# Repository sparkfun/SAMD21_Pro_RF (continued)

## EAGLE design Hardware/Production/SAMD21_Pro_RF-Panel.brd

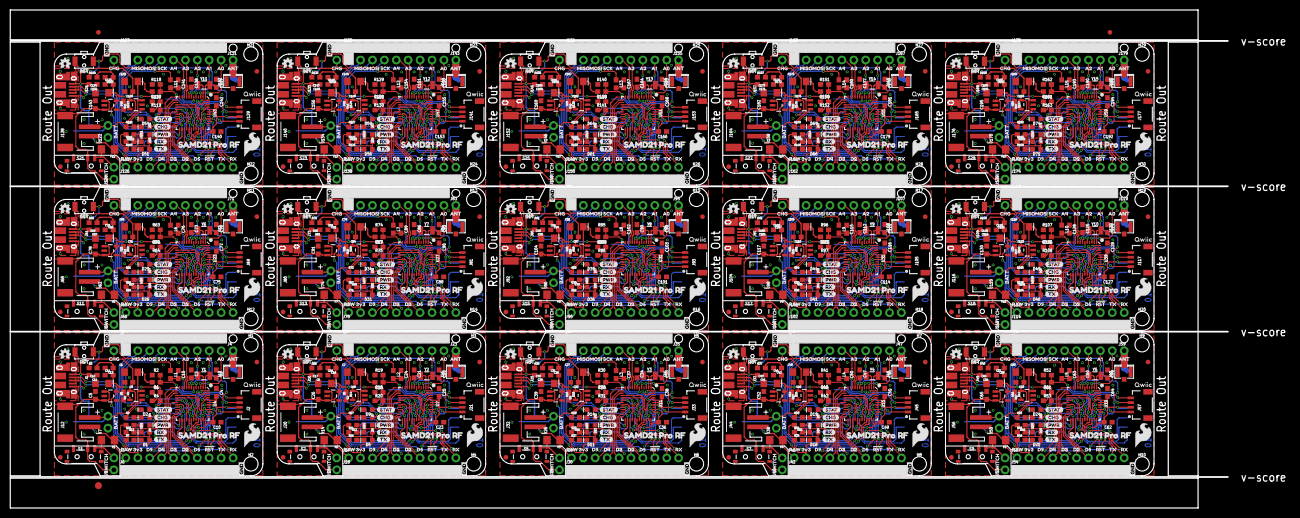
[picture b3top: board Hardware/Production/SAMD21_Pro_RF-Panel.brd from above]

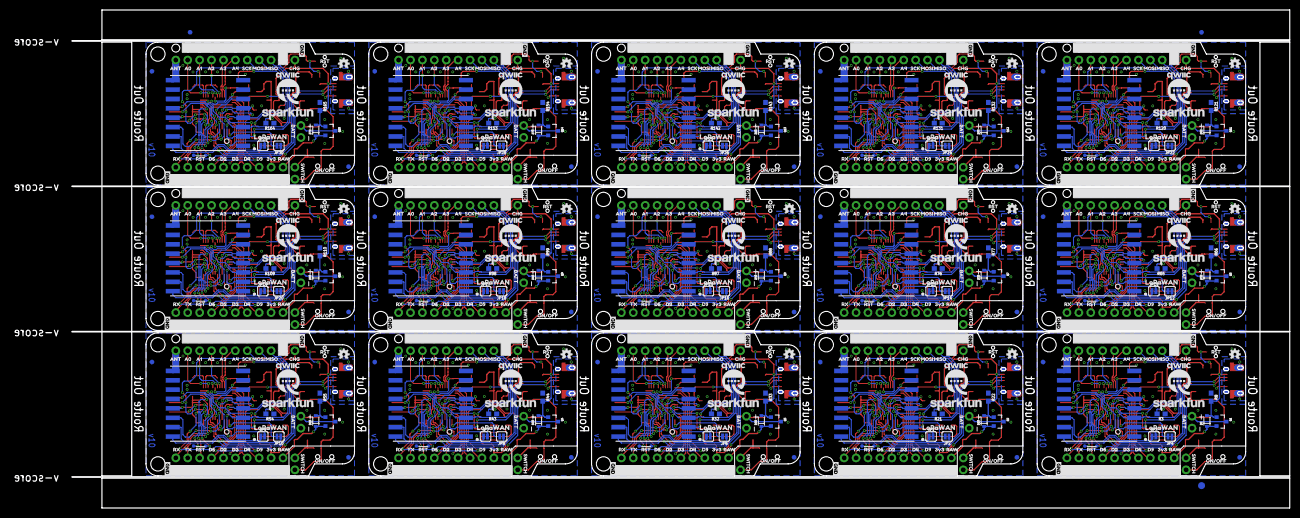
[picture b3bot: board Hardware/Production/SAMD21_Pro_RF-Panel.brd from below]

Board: 2 copper layers, 259.6 x 106.2 mm, 1911 parts (633 on the bottom side), 780 nets.

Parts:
C1, C7, C13, C17, C27, C30, C40, C43, C53, C56, C66, C69, C79, C82, C92, C95, C105, C108, C118, C121, C131, C134, C144, C147, C157, C160, C170, C173, C183, C186: 10uF; EIA3216
C2, C3, C20, C21, C33, C34, C46, C47, C59, C60, C72, C73, C85, C86, C98, C99, C111, C112, C124, C125, C137, C138, C150, C151, C163, C164, C176, C177, C189, C190: 15pF; 0603
C4, C6, C8, C10, C11, C14, C15, C18, C22, C23, C24, C25, C28, C31, C35, C36, C37, C38, C41, C44, C48, C49, C50, C51, C54, C57, C61, C62, C63, C64, C67, C70, C74, C75, C76, C77, C80, C83, C87, C88, C89, C90, C93, C96, C100, C101, C102, C103, C106, C109, C113, C114, C115, C116, C119, C122, C126, C127, C128, C129, C132, C135, C139, C140, C141, C142, C145, C148, C152, C153, C154, C155, C158, C161, C165, C166, C167, C168, C171, C174, C178, C179, C180, C181, C184, C187, C191, C192, C193, C194: 0.1uF; 0603
C5, C12, C16, C26, C29, C39, C42, C52, C55, C65, C68, C78, C81, C91, C94, C104, C107, C117, C120, C130, C133, C143, C146, C156, C159, C169, C172, C182, C185, C195: 1.0uF; 0603
C9, C19, C32, C45, C58, C71, C84, C97, C110, C123, C136, C149, C162, C175, C188: 4.7uF; 0603
D1, D5, D11, D16, D21, D26, D31, D36, D41, D46, D51, D56, D61, D66, D71: Green; LED-0603
D2, D4, D7, D9, D12, D14, D17, D19, D22, D24, D27, D29, D32, D34, D37, D39, D42, D44, D47, D49, D52, D54, D57, D59, D62, D64, D67, D69, D72, D74: BLUE; LED-0603
D3, D10, D15, D20, D25, D30, D35, D40, D45, D50, D55, D60, D65, D70, D75: BAT20J; SOD-323
D6, D8, D13, D18, D23, D28, D33, D38, D43, D48, D53, D58, D63, D68, D73: Yellow; LED-0603
E$1, E$2, E$3, E$4: FIDUCIAL-1X2
E$5, E$6: FIDUCIAL-1.5X3
F1, F2, F3, F4, F5, F6, F7, F8, F9, F10, F11, F12, F13, F14, F15: 6V/0.5A; 1206
FD1, FD2, FD3, FD4, FD5, FD6, FD7, FD8, FD9, FD10, FD11, FD12, FD13, FD14, FD15, FD16, FD17, FD18, FD19, FD20, FD21, FD22, FD23, FD24, FD25, FD26, FD27, FD28, FD29, FD30, FD31, FD32, FD33, FD34, FD35, FD36, FD37, FD38, FD39, FD40, FD41, FD42, FD43, FD44, FD45, FD46, FD47, FD48, FD49, FD50, FD51, FD52, FD53, FD54, FD55, FD56, FD57, FD58, FD59, FD60: FIDUCIAL1X2; FIDUCIAL-1X2
H1, H2, H3, H4, H5, H6, H7, H8, H9, H10, H11, H12, H13, H14, H15, H16, H17, H18, H19, H20, H21, H22, H23, H24, H25, H26, H27, H28, H29, H30: STAND-OFFTIGHT; STAND-OFF-TIGHT
J1, J10, J25, J37, J49, J61, J73, J85, J97, J109, J121, J133, J145, J157, J169: USB-MICROB-PTH-MILL
J2, J21, J33, J45, J57, J69, J81, J93, J105, J117, J129, J141, J153, J165, J177: 1X04_1MM_RA
J3, J6, J17, J18, J29, J30, J41, J42, J53, J54, J65, J66, J77, J78, J89, J90, J101, J102, J113, J114, J125, J126, J137, J138, J149, J150, J161, J162, J173, J174: 1X10_NO_SILK
J4, J23, J35, J47, J59, J71, J83, J95, J107, J119, J131, J143, J155, J167, J179: 1X01_NO_SILK
J5, J11, J19, J22, J31, J34, J43, J46, J55, J58, J67, J70, J79, J82, J91, J94, J103, J106, J115, J118, J127, J130, J139, J142, J151, J154, J163, J166, J175, J178: 1X09_NO_SILK
J7, J14, J26, J38, J50, J62, J74, J86, J98, J110, J122, J134, J146, J158, J170: PTH; 1X02_NO_SILK
J8, J15, J27, J39, J51, J63, J75, J87, J99, J111, J123, J135, J147, J159, J171: 1X02_NO_SILK
J9, J16, J28, J40, J52, J64, J76, J88, J100, J112, J124, J136, J148, J160, J172: External On/Off; 1X02_NO_SILK
J12, J20, J32, J44, J56, J68, J80, J92, J104, J116, J128, J140, J152, J164, J176: JST; JST-2-SMD
J13, J24, J36, J48, J60, J72, J84, J96, J108, J120, J132, J144, J156, J168, J180: U.FL
JP1, JP2, JP3, JP4, JP5, JP6, JP7, JP8, JP9, JP10, JP11, JP12, JP13, JP14, JP15, JP16, JP17, JP18, JP19, JP20, JP21, JP22, JP23, JP24, JP25, JP26, JP27, JP28, JP29, JP30: SMT-JUMPER_2_NO_SILK
L1, L2, L3, L4, L5, L6, L7, L8, L9, L10, L11, L12, L13, L14, L15: 0603
LED1, LED2, LED3, LED4, LED5, LED6, LED7, LED8, LED9, LED10, LED11, LED12, LED13, LED14, LED15: RED; LED-0603
LOGO1, LOGO3, LOGO5, LOGO7, LOGO9, LOGO11, LOGO13, LOGO15, LOGO17, LOGO19, LOGO21, LOGO23, LOGO25, LOGO27, LOGO29: OSHW-LOGOMINI; OSHW-LOGO-MINI
LOGO2, LOGO4, LOGO6, LOGO8, LOGO10, LOGO12, LOGO14, LOGO16, LOGO18, LOGO20, LOGO22, LOGO24, LOGO26, LOGO28, LOGO30: SFE_LOGO_NAME.1_INCH; SFE_LOGO_NAME_.1
Q1, Q2, Q3, Q4, Q5, Q6, Q7, Q8, Q9, Q10, Q11, Q12, Q13, Q14, Q15: 2.5A/30V; SOT23-3
R1, R2, R18, R19, R29, R30, R40, R41, R51, R52, R62, R63, R73, R74, R84, R85, R95, R96, R106, R107, R117, R118, R128, R129, R139, R140, R150, R151, R161, R162: 1M; 0603
R3, R7, R9, R10, R11, R12, R13, R16, R17, R21, R23, R24, R27, R28, R32, R34, R35, R38, R39, R43, R45, R46, R49, R50, R54, R56, R57, R60, R61, R65, R67, R68, R71, R72, R76, R78, R79, R82, R83, R87, R89, R90, R93, R94, R98, R100, R101, R104, R105, R109, R111, R112, R115, R116, R120, R122, R123, R126, R127, R131, R133, R134, R137, R138, R142, R144, R145, R148, R149, R153, R155, R156, R159, R160, R164: 1k; 0603
R4, R6, R8, R15, R20, R22, R26, R31, R33, R37, R42, R44, R48, R53, R55, R59, R64, R66, R70, R75, R77, R81, R86, R88, R92, R97, R99, R103, R108, R110, R114, R119, R121, R125, R130, R132, R136, R141, R143, R147, R152, R154, R158, R163, R165: 10k; 0603
R5, R14, R25, R36, R47, R58, R69, R80, R91, R102, R113, R124, R135, R146, R157: 2.0k; 0603
S1, S2, S5, S7, S9, S11, S13, S15, S17, S19, S21, S23, S25, S27, S29: Power; SWITCH_SPST_SMD_A
S3, S4, S6, S8, S10, S12, S14, S16, S18, S20, S22, S24, S26, S28, S30: TACTILE_SWITCH_SMD_RIGHT_ANGLE
TP1, TP2, TP3, TP4, TP5, TP6, TP7, TP8, TP9, TP10, TP11, TP12, TP13, TP14, TP15, TP16, TP17, TP18, TP19, TP20, TP21, TP22, TP23, TP24, TP25, TP26, TP27, TP28, TP29, TP30: TEST-POINT3; PAD.03X.03
U1, U2, U9, U13, U17, U21, U25, U29, U33, U37, U41, U45, U49, U53, U57: MCP73831; SOT23-5
U3, U8, U12, U16, U20, U24, U28, U32, U36, U40, U44, U48, U52, U56, U60: RFM95W; RFM95/96/97/98W
U4, U7, U11, U15, U19, U23, U27, U31, U35, U39, U43, U47, U51, U55, U59: ATSAMD21G; QFN-48_NO_EXPOSED_PAD
U5, U6, U10, U14, U18, U22, U26, U30, U34, U38, U42, U46, U50, U54, U58: 3.3V; SOT23-5
U$1, U$114, U$177, U$240, U$303, U$366, U$429, U$492, U$555, U$618, U$681, U$744, U$807, U$870, U$933: SAMD21_PRO_RF0
U$2, U$18, U$115, U$119, U$178, U$182, U$241, U$245, U$304, U$308, U$367, U$371, U$430, U$434, U$493, U$497, U$556, U$560, U$619, U$623, U$682, U$686, U$745, U$749, U$808, U$812, U$871, U$875, U$934, U$938: D20
U$3, U$26, U$42, U$88, U$127, U$151, U$190, U$214, U$253, U$277, U$316, U$340, U$379, U$403, U$442, U$466, U$505, U$529, U$568, U$592, U$631, U$655, U$694, U$718, U$757, U$781, U$820, U$844, U$883, U$907: A43
U$4, U$34, U$43, U$89, U$128, U$152, U$191, U$215, U$254, U$278, U$317, U$341, U$380, U$404, U$443, U$467, U$506, U$530, U$569, U$593, U$632, U$656, U$695, U$719, U$758, U$782, U$821, U$845, U$884, U$908: A34
U$5, U$44, U$56, U$90, U$129, U$153, U$192, U$216, U$255, U$279, U$318, U$342, U$381, U$405, U$444, U$468, U$507, U$531, U$570, U$594, U$633, U$657, U$696, U$720, U$759, U$783, U$822, U$846, U$885, U$909: A25
U$6, U$45, U$58, U$91, U$130, U$154, U$193, U$217, U$256, U$280, U$319, U$343, U$382, U$406, U$445, U$469, U$508, U$532, U$571, U$595, U$634, U$658, U$697, U$721, U$760, U$784, U$823, U$847, U$886, U$910: A16
U$7, U$46, U$59, U$92, U$131, U$155, U$194, U$218, U$257, U$281, U$320, U$344, U$383, U$407, U$446, U$470, U$509, U$533, U$572, U$596, U$635, U$659, U$698, U$722, U$761, U$785, U$824, U$848, U$887, U$911: A07
U$8, U$47, U$64, U$93, U$132, U$156, U$195, U$219, U$258, U$282, U$321, U$345, U$384, U$408, U$447, U$471, U$510, U$534, U$573, U$597, U$636, U$660, U$699, U$723, U$762, U$786, U$825, U$849, U$888, U$912: MISO8
U$9, U$48, U$66, U$94, U$133, U$157, U$196, U$220, U$259, U$283, U$322, U$346, U$385, U$409, U$448, U$472, U$511, U$535, U$574, U$598, U$637, U$661, U$700, U$724, U$763, U$787, U$826, U$850, U$889, U$913: MOSI9
U$10, U$49, U$67, U$95, U$134, U$158, U$197, U$221, U$260, U$284, U$323, U$347, U$386, U$410, U$449, U$473, U$512, U$536, U$575, U$599, U$638, U$662, U$701, U$725, U$764, U$788, U$827, U$851, U$890, U$914: SCK10
U$11, U$50, U$68, U$96, U$135, U$159, U$198, U$222, U$261, U$285, U$324, U$348, U$387, U$411, U$450, U$474, U$513, U$537, U$576, U$600, U$639, U$663, U$702, U$726, U$765, U$789, U$828, U$852, U$891, U$915: ANT11
U$12, U$17, U$38, U$62, U$71, U$84, U$99, U$109, U$136, U$147, U$162, U$172, U$199, U$210, U$225, U$235, U$262, U$273, U$288, U$298, U$325, U$336, U$351, U$361, U$388, U$399, U$414, U$424, U$451, U$462, U$477, U$487, U$514, U$525, U$540, U$550, U$577, U$588, U$603, U$613, U$640, U$651, U$666, U$676, U$703, U$714, U$729, U$739, U$766, U$777, U$792, U$802, U$829, U$840, U$855, U$865, U$892, U$903, U$918, U$928: GND0
U$13, U$28, U$36, U$41, U$74, U$79, U$82, U$87, U$137, U$142, U$145, U$150, U$200, U$205, U$208, U$213, U$263, U$268, U$271, U$276, U$326, U$331, U$334, U$339, U$389, U$394, U$397, U$402, U$452, U$457, U$460, U$465, U$515, U$520, U$523, U$528, U$578, U$583, U$586, U$591, U$641, U$646, U$649, U$654, U$704, U$709, U$712, U$717, U$767, U$772, U$775, U$780, U$830, U$835, U$838, U$843, U$893, U$898, U$901, U$906: RST2
U$14, U$40, U$65, U$75, U$86, U$105, U$138, U$149, U$168, U$201, U$212, U$231, U$264, U$275, U$294, U$327, U$338, U$357, U$390, U$401, U$420, U$453, U$464, U$483, U$516, U$527, U$546, U$579, U$590, U$609, U$642, U$653, U$672, U$705, U$716, U$735, U$768, U$779, U$798, U$831, U$842, U$861, U$894, U$905, U$924: CHG1
U$15, U$16, U$107, U$108, U$170, U$171, U$233, U$234, U$296, U$297, U$359, U$360, U$422, U$423, U$485, U$486, U$548, U$549, U$611, U$612, U$674, U$675, U$737, U$738, U$800, U$801, U$863, U$864, U$926, U$927: D90
U$19, U$73, U$104, U$110, U$167, U$173, U$230, U$236, U$293, U$299, U$356, U$362, U$419, U$425, U$482, U$488, U$545, U$551, U$608, U$614, U$671, U$677, U$734, U$740, U$797, U$803, U$860, U$866, U$923, U$929: RX2
U$20, U$21, U$116, U$120, U$179, U$183, U$242, U$246, U$305, U$309, U$368, U$372, U$431, U$435, U$494, U$498, U$557, U$561, U$620, U$624, U$683, U$687, U$746, U$750, U$809, U$813, U$872, U$876, U$935, U$939: D30
U$22, U$31, U$117, U$121, U$180, U$184, U$243, U$247, U$306, U$310, U$369, U$373, U$432, U$436, U$495, U$499, U$558, U$562, U$621, U$625, U$684, U$688, U$747, U$751, U$810, U$814, U$873, U$877, U$936, U$940: D40
U$23, U$53, U$76, U$98, U$139, U$161, U$202, U$224, U$265, U$287, U$328, U$350, U$391, U$413, U$454, U$476, U$517, U$539, U$580, U$602, U$643, U$665, U$706, U$728, U$769, U$791, U$832, U$854, U$895, U$917: 3V320
U$24, U$52, U$77, U$97, U$140, U$160, U$203, U$223, U$266, U$286, U$329, U$349, U$392, U$412, U$455, U$475, U$518, U$538, U$581, U$601, U$644, U$664, U$707, U$727, U$770, U$790, U$833, U$853, U$896, U$916: RAW21
U$25, U$112, U$175, U$238, U$301, U$364, U$427, U$490, U$553, U$616, U$679, U$742, U$805, U$868, U$931: LORA0
U$27, U$37, U$78, U$83, U$141, U$146, U$204, U$209, U$267, U$272, U$330, U$335, U$393, U$398, U$456, U$461, U$519, U$524, U$582, U$587, U$645, U$650, U$708, U$713, U$771, U$776, U$834, U$839, U$897, U$902: SWITCH23
U$29, U$32, U$80, U$81, U$143, U$144, U$206, U$207, U$269, U$270, U$332, U$333, U$395, U$396, U$458, U$459, U$521, U$522, U$584, U$585, U$647, U$648, U$710, U$711, U$773, U$774, U$836, U$837, U$899, U$900: BATT25
U$30, U$122, U$185, U$248, U$311, U$374, U$437, U$500, U$563, U$626, U$689, U$752, U$815, U$878, U$941: QWIIC-LOGO-MEDIUM
U$33, U$118, U$181, U$244, U$307, U$370, U$433, U$496, U$559, U$622, U$685, U$748, U$811, U$874, U$937: D50
U$35, U$113, U$176, U$239, U$302, U$365, U$428, U$491, U$554, U$617, U$680, U$743, U$806, U$869, U$932: WAN1
U$39, U$85, U$148, U$211, U$274, U$337, U$400, U$463, U$526, U$589, U$652, U$715, U$778, U$841, U$904: ON#OFF0
U$51, U$126, U$189, U$252, U$315, U$378, U$441, U$504, U$567, U$630, U$693, U$756, U$819, U$882, U$945: SFE_LOGO_FLAME_.2
U$54, U$125, U$188, U$251, U$314, U$377, U$440, U$503, U$566, U$629, U$692, U$755, U$818, U$881, U$944: STAT0
U$55, U$106, U$169, U$232, U$295, U$358, U$421, U$484, U$547, U$610, U$673, U$736, U$799, U$862, U$925: D514
U$57, U$69, U$101, U$111, U$164, U$174, U$227, U$237, U$290, U$300, U$353, U$363, U$416, U$426, U$479, U$489, U$542, U$552, U$605, U$615, U$668, U$678, U$731, U$741, U$794, U$804, U$857, U$867, U$920, U$930: TX3
U$60, U$123, U$186, U$249, U$312, U$375, U$438, U$501, U$564, U$627, U$690, U$753, U$816, U$879, U$942: QWIIC-TEXT-04
U$61, U$124, U$187, U$250, U$313, U$376, U$439, U$502, U$565, U$628, U$691, U$754, U$817, U$880, U$943: OSHW-LOGO-MINI
U$63, U$100, U$163, U$226, U$289, U$352, U$415, U$478, U$541, U$604, U$667, U$730, U$793, U$856, U$919: PWR-()-03
U$70, U$102, U$165, U$228, U$291, U$354, U$417, U$480, U$543, U$606, U$669, U$732, U$795, U$858, U$921: TX6
U$72, U$103, U$166, U$229, U$292, U$355, U$418, U$481, U$544, U$607, U$670, U$733, U$796, U$859, U$922: RX7
Y1, Y2, Y3, Y4, Y5, Y6, Y7, Y8, Y9, Y10, Y11, Y12, Y13, Y14, Y15: 32.768kHz; CRYSTAL-SMD-3.2X1.5MM

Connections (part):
3.3V: C4.2, C6.2, C10.2, C12.1, C13.+, C14.2, D1.A, D6.A, J2.2, J3.2, L1.1, R4.2, R6.2, R13.2, U3.3.3V, U4.17, U4.36, U4.43, U4.44, U6.5
3.3V1: C16.1, C17.+, C18.2, C22.2, C23.2, C25.2, D5.A, D8.A, J17.2, J21.2, L2.1, R12.2, R15.2, R20.2, U5.5, U7.17, U7.36, U7.43, U7.44, U8.3.3V
3.3V2: C29.1, C30.+, C31.2, C35.2, C36.2, C38.2, D11.A, D13.A, J29.2, J33.2, L3.1, R24.2, R26.2, R31.2, U10.5, U11.17, U11.36, U11.43, U11.44, U12.3.3V
3.3V3: C42.1, C43.+, C44.2, C48.2, C49.2, C51.2, D16.A, D18.A, J41.2, J45.2, L4.1, R35.2, R37.2, R42.2, U14.5, U15.17, U15.36, U15.43, U15.44, U16.3.3V
3.3V4: C55.1, C56.+, C57.2, C61.2, C62.2, C64.2, D21.A, D23.A, J53.2, J57.2, L5.1, R46.2, R48.2, R53.2, U18.5, U19.17, U19.36, U19.43, U19.44, U20.3.3V
3.3V5: C68.1, C69.+, C70.2, C74.2, C75.2, C77.2, D26.A, D28.A, J65.2, J69.2, L6.1, R57.2, R59.2, R64.2, U22.5, U23.17, U23.36, U23.43, U23.44, U24.3.3V
3.3V6: C81.1, C82.+, C83.2, C87.2, C88.2, C90.2, D31.A, D33.A, J77.2, J81.2, L7.1, R68.2, R70.2, R75.2, U26.5, U27.17, U27.36, U27.43, U27.44, U28.3.3V
3.3V7: C94.1, C95.+, C96.2, C100.2, C101.2, C103.2, D36.A, D38.A, J89.2, J93.2, L8.1, R79.2, R81.2, R86.2, U30.5, U31.17, U31.36, U31.43, U31.44, U32.3.3V
3.3V8: C107.1, C108.+, C109.2, C113.2, C114.2, C116.2, D41.A, D43.A, J101.2, J105.2, L9.1, R90.2, R92.2, R97.2, U34.5, U35.17, U35.36, U35.43, U35.44, U36.3.3V
3.3V9: C120.1, C121.+, C122.2, C126.2, C127.2, C129.2, D46.A, D48.A, J113.2, J117.2, L10.1, R101.2, R103.2, R108.2, U38.5, U39.17, U39.36, U39.43, U39.44, U40.3.3V
3.3V10: C133.1, C134.+, C135.2, C139.2, C140.2, C142.2, D51.A, D53.A, J125.2, J129.2, L11.1, R112.2, R114.2, R119.2, U42.5, U43.17, U43.36, U43.43, U43.44, U44.3.3V
3.3V11: C146.1, C147.+, C148.2, C152.2, C153.2, C155.2, D56.A, D58.A, J137.2, J141.2, L12.1, R123.2, R125.2, R130.2, U46.5, U47.17, U47.36, U47.43, U47.44, U48.3.3V
3.3V12: C159.1, C160.+, C161.2, C165.2, C166.2, C168.2, D61.A, D63.A, J149.2, J153.2, L13.1, R134.2, R136.2, R141.2, U50.5, U51.17, U51.36, U51.43, U51.44, U52.3.3V
3.3V13: C172.1, C173.+, C174.2, C178.2, C179.2, C181.2, D66.A, D68.A, J161.2, J165.2, L14.1, R145.2, R147.2, R152.2, U54.5, U55.17, U55.36, U55.43, U55.44, U56.3.3V
3.3V14: C185.1, C186.+, C187.2, C191.2, C192.2, C194.2, D71.A, D73.A, J173.2, J177.2, L15.1, R156.2, R158.2, R163.2, U58.5, U59.17, U59.36, U59.43, U59.44, U60.3.3V
!RFM_CS: R4.1, U3.NSS, U4.28
!RFM_CS1: R20.1, U7.28, U8.NSS
!RFM_CS2: R31.1, U11.28, U12.NSS
!RFM_CS3: R42.1, U15.28, U16.NSS
!RFM_CS4: R53.1, U19.28, U20.NSS
!RFM_CS5: R64.1, U23.28, U24.NSS
!RFM_CS6: R75.1, U27.28, U28.NSS
!RFM_CS7: R86.1, U31.28, U32.NSS
!RFM_CS8: R97.1, U35.28, U36.NSS
!RFM_CS9: R108.1, U39.28, U40.NSS
!RFM_CS10: R119.1, U43.28, U44.NSS
!RFM_CS11: R130.1, U47.28, U48.NSS
!RFM_CS12: R141.1, U51.28, U52.NSS
!RFM_CS13: R152.1, U55.28, U56.NSS
!RFM_CS14: R163.1, U59.28, U60.NSS
!RFM_RST: U3.!RESET, U4.30
!RFM_RST1: U7.30, U8.!RESET
!RFM_RST2: U11.30, U12.!RESET
!RFM_RST3: U15.30, U16.!RESET
!RFM_RST4: U19.30, U20.!RESET
!RFM_RST5: U23.30, U24.!RESET
!RFM_RST6: U27.30, U28.!RESET
!RFM_RST7: U31.30, U32.!RESET
!RFM_RST8: U35.30, U36.!RESET
!RFM_RST9: U39.30, U40.!RESET
!RFM_RST10: U43.30, U44.!RESET
!RFM_RST11: U47.30, U48.!RESET
!RFM_RST12: U51.30, U52.!RESET
!RFM_RST13: U55.30, U56.!RESET
!RFM_RST14: U59.30, U60.!RESET
!RST: J3.8, R6.1, S3.1, U4.40
!RST1: J17.8, R15.1, S4.1, U7.40
!RST2: J29.8, R26.1, S6.1, U11.40
!RST3: J41.8, R37.1, S8.1, U15.40
!RST4: J53.8, R48.1, S10.1, U19.40
!RST5: J65.8, R59.1, S12.1, U23.40
!RST6: J77.8, R70.1, S14.1, U27.40
!RST7: J89.8, R81.1, S16.1, U31.40
!RST8: J101.8, R92.1, S18.1, U35.40
!RST9: J113.8, R103.1, S20.1, U39.40
!RST10: J125.8, R114.1, S22.1, U43.40
!RST11: J137.8, R125.1, S24.1, U47.40
!RST12: J149.8, R136.1, S26.1, U51.40
!RST13: J161.8, R147.1, S28.1, U55.40
!RST14: J173.8, R158.1, S30.1, U59.40
A0: J11.9, U4.3
A1: J11.8, U4.7
A2: J11.7, U4.8
A3: J11.6, U4.9
A4: J11.5, U4.10
A5: J22.9, U7.3
A6: J22.8, U7.7
A7: J22.7, U7.8
A8: J22.6, U7.9
A9: J22.5, U7.10
A10: J34.9, U11.3
A11: J34.8, U11.7
A12: J34.7, U11.8
A13: J34.6, U11.9
A14: J34.5, U11.10
A15: J46.9, U15.3
A16: J46.8, U15.7
A17: J46.7, U15.8
A18: J46.6, U15.9
A19: J46.5, U15.10
A20: J58.9, U19.3
A21: J58.8, U19.7
A22: J58.7, U19.8
A23: J58.6, U19.9
A24: J58.5, U19.10
A25: J70.9, U23.3
A26: J70.8, U23.7
A27: J70.7, U23.8
A28: J70.6, U23.9
A29: J70.5, U23.10
A30: J82.9, U27.3
A31: J82.8, U27.7
A32: J82.7, U27.8
A33: J82.6, U27.9
A34: J82.5, U27.10
A35: J94.9, U31.3
A36: J94.8, U31.7
A37: J94.7, U31.8
A38: J94.6, U31.9
A39: J94.5, U31.10
A40: J106.9, U35.3
A41: J106.8, U35.7
A42: J106.7, U35.8
A43: J106.6, U35.9
A44: J106.5, U35.10
A45: J118.9, U39.3
A46: J118.8, U39.7
A47: J118.7, U39.8
A48: J118.6, U39.9
A49: J118.5, U39.10
A50: J130.9, U43.3
A51: J130.8, U43.7
A52: J130.7, U43.8
A53: J130.6, U43.9
A54: J130.5, U43.10
A55: J142.9, U47.3
A56: J142.8, U47.7
A57: J142.7, U47.8
A58: J142.6, U47.9
A59: J142.5, U47.10
A60: J154.9, U51.3
A61: J154.8, U51.7
A62: J154.7, U51.8
A63: J154.6, U51.9
A64: J154.5, U51.10
A65: J166.9, U55.3
A66: J166.8, U55.7
A67: J166.7, U55.8
A68: J166.6, U55.9
A69: J166.5, U55.10
A70: J178.9, U59.3
A71: J178.8, U59.7
A72: J178.7, U59.8
A73: J178.6, U59.9
A74: J178.5, U59.10
ANT: J4.1, J13.FEED, U3.ANT
ANT1: J23.1, J24.FEED, U8.ANT
ANT2: J35.1, J36.FEED, U12.ANT
ANT3: J47.1, J48.FEED, U16.ANT
ANT4: J59.1, J60.FEED, U20.ANT
ANT5: J71.1, J72.FEED, U24.ANT
ANT6: J83.1, J84.FEED, U28.ANT
ANT7: J95.1, J96.FEED, U32.ANT
ANT8: J107.1, J108.FEED, U36.ANT
ANT9: J119.1, J120.FEED, U40.ANT
ANT10: J131.1, J132.FEED, U44.ANT
ANT11: J143.1, J144.FEED, U48.ANT
ANT12: J155.1, J156.FEED, U52.ANT
ANT13: J167.1, J168.FEED, U56.ANT
ANT14: J179.1, J180.FEED, U60.ANT
CHARGE_STAT: R9.1, U1.1
CHARGE_STAT1: R17.1, U2.1
CHARGE_STAT2: R28.1, U9.1
CHARGE_STAT3: R39.1, U13.1
CHARGE_STAT4: R50.1, U17.1
CHARGE_STAT5: R61.1, U21.1
CHARGE_STAT6: R72.1, U25.1
CHARGE_STAT7: R83.1, U29.1
CHARGE_STAT8: R94.1, U33.1
CHARGE_STAT9: R105.1, U37.1
CHARGE_STAT10: R116.1, U41.1
CHARGE_STAT11: R127.1, U45.1
CHARGE_STAT12: R138.1, U49.1
CHARGE_STAT13: R149.1, U53.1
CHARGE_STAT14: R160.1, U57.1
D1: J17.4, U7.13
D2: J3.6, U4.23
D3: J3.5, U4.14
D4: J3.4, U4.13
D5: J3.7, U4.24
D6: J17.6, U7.23
D7: J17.5, U7.14
D8: J17.7, U7.24
D9: J3.3, U4.12
D10: J17.3, U7.12
D10_LORA-WAN: JP3.2, U4.27
D10_LORA-WAN1: JP1.2, U7.27
D10_LORA-WAN2: JP5.2, U11.27
D10_LORA-WAN3: JP7.2, U15.27
D10_LORA-WAN4: JP9.2, U19.27
D10_LORA-WAN5: JP11.2, U23.27
D10_LORA-WAN6: JP13.2, U27.27
D10_LORA-WAN7: JP15.2, U31.27
D10_LORA-WAN8: JP17.2, U35.27
D10_LORA-WAN9: JP19.2, U39.27
D10_LORA-WAN10: JP21.2, U43.27
D10_LORA-WAN11: JP23.2, U47.27
D10_LORA-WAN12: JP25.2, U51.27
D10_LORA-WAN13: JP27.2, U55.27
D10_LORA-WAN14: JP29.2, U59.27
D11: J29.4, U11.13
D11_LORA-WAN: JP4.2, U4.25
D11_LORA-WAN1: JP2.2, U7.25
D11_LORA-WAN2: JP6.2, U11.25
D11_LORA-WAN3: JP8.2, U15.25
D11_LORA-WAN4: JP10.2, U19.25
D11_LORA-WAN5: JP12.2, U23.25
D11_LORA-WAN6: JP14.2, U27.25
D11_LORA-WAN7: JP16.2, U31.25
D11_LORA-WAN8: JP18.2, U35.25
D11_LORA-WAN9: JP20.2, U39.25
D11_LORA-WAN10: JP22.2, U43.25
D11_LORA-WAN11: JP24.2, U47.25
D11_LORA-WAN12: JP26.2, U51.25
D11_LORA-WAN13: JP28.2, U55.25
D11_LORA-WAN14: JP30.2, U59.25
D12: J29.6, U11.23
D13: J29.5, U11.14
D14: J29.7, U11.24
D15: J29.3, U11.12
D16: J41.4, U15.13
D17: J41.6, U15.23
D18: J41.5, U15.14
D19: J41.7, U15.24
D20: J41.3, U15.12
D21: J53.4, U19.13
D22: J53.6, U19.23
D23: J53.5, U19.14
D24: J53.7, U19.24
D25: J53.3, U19.12
D26: J65.4, U23.13
D27: J65.6, U23.23
D28: J65.5, U23.14
D29: J65.7, U23.24
D30: J65.3, U23.12
D31: J77.4, U27.13
D32: J77.6, U27.23
D33: J77.5, U27.14
D34: J77.7, U27.24
D35: J77.3, U27.12
D36: J89.4, U31.13
D37: J89.6, U31.23
D38: J89.5, U31.14
D39: J89.7, U31.24
D40: J89.3, U31.12
D41: J101.4, U35.13
D42: J101.6, U35.23
D43: J101.5, U35.14
D44: J101.7, U35.24
D45: J101.3, U35.12
D46: J113.4, U39.13
D47: J113.6, U39.23
D48: J113.5, U39.14
D49: J113.7, U39.24
D50: J113.3, U39.12
D51: J125.4, U43.13
D52: J125.6, U43.23
D53: J125.5, U43.14
D54: J125.7, U43.24
D55: J125.3, U43.12
D56: J137.4, U47.13
D57: J137.6, U47.23
D58: J137.5, U47.14
D59: J137.7, U47.24
D60: J137.3, U47.12
D61: J149.4, U51.13
D62: J149.6, U51.23
D63: J149.5, U51.14
D64: J149.7, U51.24
D65: J149.3, U51.12
D66: J161.4, U55.13
D67: J161.6, U55.23
D68: J161.5, U55.14
D69: J161.7, U55.24
D70: J161.3, U55.12
D71: J173.4, U59.13
D72: J173.6, U59.23
D73: J173.5, U59.14
D74: J173.7, U59.24
D75: J173.3, U59.12
D+: J1.D+, U4.34
D+1: J10.D+, U7.34
D+2: J25.D+, U11.34
D+3: J37.D+, U15.34
D+4: J49.D+, U19.34
D+5: J61.D+, U23.34
D+6: J73.D+, U27.34
D+7: J85.D+, U31.34
D+8: J97.D+, U35.34
D+9: J109.D+, U39.34
D+10: J121.D+, U43.34
D+11: J133.D+, U47.34
D+12: J145.D+, U51.34
D+13: J157.D+, U55.34
D+14: J169.D+, U59.34
D-: J1.D-, U4.33
D-1: J10.D-, U7.33
D-2: J25.D-, U11.33
D-3: J37.D-, U15.33
D-4: J49.D-, U19.33
D-5: J61.D-, U23.33
D-6: J73.D-, U27.33
D-7: J85.D-, U31.33
D-8: J97.D-, U35.33
D-9: J109.D-, U39.33
D-10: J121.D-, U43.33
D-11: J133.D-, U47.33
D-12: J145.D-, U51.33
D-13: J157.D-, U55.33
D-14: J169.D-, U59.33
GND: C1.-, C2.1, C3.1, C4.1, C5.2, C6.1, C9.2, C10.1, C11.1, C12.2, C13.-, C14.1, C15.1, J1.GND, J2.1, J5.1, J5.2, J5.3, J5.4, J5.5, J5.6, J5.7, J5.8, J5.9, J6.1, J6.2, J6.3, J6.4, J6.5, J6.6, J6.7, J6.8, J6.9, J6.10, J7.1, J8.1, J11.1, J12.1, J13.1, J13.2, LED1.C, R2.1, R3.1, R5.2, R8.1, S3.2, U1.2, U3.GND@1, U3.GND@2, U3.GND@3, U4.5, U4.18, U4.35, U4.42, U6.2
GND1: C7.-, C8.1, C16.2, C17.-, C18.1, C19.2, C20.1, C21.1, C22.1, C23.1, C24.1, C25.1, C26.2, J10.GND, J14.1, J15.1, J18.1, J18.2, J18.3, J18.4, J18.5, J18.6, J18.7, J18.8, J18.9, J18.10, J19.1, J19.2, J19.3, J19.4, J19.5, J19.6, J19.7, J19.8, J19.9, J20.1, J21.1, J22.1, J24.1, J24.2, LED2.C, R14.2, R19.1, R21.1, R22.1, S4.2, U2.2, U5.2, U7.5, U7.18, U7.35, U7.42, U8.GND@1, U8.GND@2, U8.GND@3
GND2: C27.-, C28.1, C29.2, C30.-, C31.1, C32.2, C33.1, C34.1, C35.1, C36.1, C37.1, C38.1, C39.2, J25.GND, J26.1, J27.1, J30.1, J30.2, J30.3, J30.4, J30.5, J30.6, J30.7, J30.8, J30.9, J30.10, J31.1, J31.2, J31.3, J31.4, J31.5, J31.6, J31.7, J31.8, J31.9, J32.1, J33.1, J34.1, J36.1, J36.2, LED3.C, R25.2, R30.1, R32.1, R33.1, S6.2, U9.2, U10.2, U11.5, U11.18, U11.35, U11.42, U12.GND@1, U12.GND@2, U12.GND@3
GND3: C40.-, C41.1, C42.2, C43.-, C44.1, C45.2, C46.1, C47.1, C48.1, C49.1, C50.1, C51.1, C52.2, J37.GND, J38.1, J39.1, J42.1, J42.2, J42.3, J42.4, J42.5, J42.6, J42.7, J42.8, J42.9, J42.10, J43.1, J43.2, J43.3, J43.4, J43.5, J43.6, J43.7, J43.8, J43.9, J44.1, J45.1, J46.1, J48.1, J48.2, LED4.C, R36.2, R41.1, R43.1, R44.1, S8.2, U13.2, U14.2, U15.5, U15.18, U15.35, U15.42, U16.GND@1, U16.GND@2, U16.GND@3
GND4: C53.-, C54.1, C55.2, C56.-, C57.1, C58.2, C59.1, C60.1, C61.1, C62.1, C63.1, C64.1, C65.2, J49.GND, J50.1, J51.1, J54.1, J54.2, J54.3, J54.4, J54.5, J54.6, J54.7, J54.8, J54.9, J54.10, J55.1, J55.2, J55.3, J55.4, J55.5, J55.6, J55.7, J55.8, J55.9, J56.1, J57.1, J58.1, J60.1, J60.2, LED5.C, R47.2, R52.1, R54.1, R55.1, S10.2, U17.2, U18.2, U19.5, U19.18, U19.35, U19.42, U20.GND@1, U20.GND@2, U20.GND@3
GND5: C66.-, C67.1, C68.2, C69.-, C70.1, C71.2, C72.1, C73.1, C74.1, C75.1, C76.1, C77.1, C78.2, J61.GND, J62.1, J63.1, J66.1, J66.2, J66.3, J66.4, J66.5, J66.6, J66.7, J66.8, J66.9, J66.10, J67.1, J67.2, J67.3, J67.4, J67.5, J67.6, J67.7, J67.8, J67.9, J68.1, J69.1, J70.1, J72.1, J72.2, LED6.C, R58.2, R63.1, R65.1, R66.1, S12.2, U21.2, U22.2, U23.5, U23.18, U23.35, U23.42, U24.GND@1, U24.GND@2, U24.GND@3
GND6: C79.-, C80.1, C81.2, C82.-, C83.1, C84.2, C85.1, C86.1, C87.1, C88.1, C89.1, C90.1, C91.2, J73.GND, J74.1, J75.1, J78.1, J78.2, J78.3, J78.4, J78.5, J78.6, J78.7, J78.8, J78.9, J78.10, J79.1, J79.2, J79.3, J79.4, J79.5, J79.6, J79.7, J79.8, J79.9, J80.1, J81.1, J82.1, J84.1, J84.2, LED7.C, R69.2, R74.1, R76.1, R77.1, S14.2, U25.2, U26.2, U27.5, U27.18, U27.35, U27.42, U28.GND@1, U28.GND@2, U28.GND@3
GND7: C92.-, C93.1, C94.2, C95.-, C96.1, C97.2, C98.1, C99.1, C100.1, C101.1, C102.1, C103.1, C104.2, J85.GND, J86.1, J87.1, J90.1, J90.2, J90.3, J90.4, J90.5, J90.6, J90.7, J90.8, J90.9, J90.10, J91.1, J91.2, J91.3, J91.4, J91.5, J91.6, J91.7, J91.8, J91.9, J92.1, J93.1, J94.1, J96.1, J96.2, LED8.C, R80.2, R85.1, R87.1, R88.1, S16.2, U29.2, U30.2, U31.5, U31.18, U31.35, U31.42, U32.GND@1, U32.GND@2, U32.GND@3
GND8: C105.-, C106.1, C107.2, C108.-, C109.1, C110.2, C111.1, C112.1, C113.1, C114.1, C115.1, C116.1, C117.2, J97.GND, J98.1, J99.1, J102.1, J102.2, J102.3, J102.4, J102.5, J102.6, J102.7, J102.8, J102.9, J102.10, J103.1, J103.2, J103.3, J103.4, J103.5, J103.6, J103.7, J103.8, J103.9, J104.1, J105.1, J106.1, J108.1, J108.2, LED9.C, R91.2, R96.1, R98.1, R99.1, S18.2, U33.2, U34.2, U35.5, U35.18, U35.35, U35.42, U36.GND@1, U36.GND@2, U36.GND@3
GND9: C118.-, C119.1, C120.2, C121.-, C122.1, C123.2, C124.1, C125.1, C126.1, C127.1, C128.1, C129.1, C130.2, J109.GND, J110.1, J111.1, J114.1, J114.2, J114.3, J114.4, J114.5, J114.6, J114.7, J114.8, J114.9, J114.10, J115.1, J115.2, J115.3, J115.4, J115.5, J115.6, J115.7, J115.8, J115.9, J116.1, J117.1, J118.1, J120.1, J120.2, LED10.C, R102.2, R107.1, R109.1, R110.1, S20.2, U37.2, U38.2, U39.5, U39.18, U39.35, U39.42, U40.GND@1, U40.GND@2, U40.GND@3
GND10: C131.-, C132.1, C133.2, C134.-, C135.1, C136.2, C137.1, C138.1, C139.1, C140.1, C141.1, C142.1, C143.2, J121.GND, J122.1, J123.1, J126.1, J126.2, J126.3, J126.4, J126.5, J126.6, J126.7, J126.8, J126.9, J126.10, J127.1, J127.2, J127.3, J127.4, J127.5, J127.6, J127.7, J127.8, J127.9, J128.1, J129.1, J130.1, J132.1, J132.2, LED11.C, R113.2, R118.1, R120.1, R121.1, S22.2, U41.2, U42.2, U43.5, U43.18, U43.35, U43.42, U44.GND@1, U44.GND@2, U44.GND@3
GND11: C144.-, C145.1, C146.2, C147.-, C148.1, C149.2, C150.1, C151.1, C152.1, C153.1, C154.1, C155.1, C156.2, J133.GND, J134.1, J135.1, J138.1, J138.2, J138.3, J138.4, J138.5, J138.6, J138.7, J138.8, J138.9, J138.10, J139.1, J139.2, J139.3, J139.4, J139.5, J139.6, J139.7, J139.8, J139.9, J140.1, J141.1, J142.1, J144.1, J144.2, LED12.C, R124.2, R129.1, R131.1, R132.1, S24.2, U45.2, U46.2, U47.5, U47.18, U47.35, U47.42, U48.GND@1, U48.GND@2, U48.GND@3
GND12: C157.-, C158.1, C159.2, C160.-, C161.1, C162.2, C163.1, C164.1, C165.1, C166.1, C167.1, C168.1, C169.2, J145.GND, J146.1, J147.1, J150.1, J150.2, J150.3, J150.4, J150.5, J150.6, J150.7, J150.8, J150.9, J150.10, J151.1, J151.2, J151.3, J151.4, J151.5, J151.6, J151.7, J151.8, J151.9, J152.1, J153.1, J154.1, J156.1, J156.2, LED13.C, R135.2, R140.1, R142.1, R143.1, S26.2, U49.2, U50.2, U51.5, U51.18, U51.35, U51.42, U52.GND@1, U52.GND@2, U52.GND@3
GND13: C170.-, C171.1, C172.2, C173.-, C174.1, C175.2, C176.1, C177.1, C178.1, C179.1, C180.1, C181.1, C182.2, J157.GND, J158.1, J159.1, J162.1, J162.2, J162.3, J162.4, J162.5, J162.6, J162.7, J162.8, J162.9, J162.10, J163.1, J163.2, J163.3, J163.4, J163.5, J163.6, J163.7, J163.8, J163.9, J164.1, J165.1, J166.1, J168.1, J168.2, LED14.C, R146.2, R151.1, R153.1, R154.1, S28.2, U53.2, U54.2, U55.5, U55.18, U55.35, U55.42, U56.GND@1, U56.GND@2, U56.GND@3
GND14: C183.-, C184.1, C185.2, C186.-, C187.1, C188.2, C189.1, C190.1, C191.1, C192.1, C193.1, C194.1, C195.2, J169.GND, J170.1, J171.1, J174.1, J174.2, J174.3, J174.4, J174.5, J174.6, J174.7, J174.8, J174.9, J174.10, J175.1, J175.2, J175.3, J175.4, J175.5, J175.6, J175.7, J175.8, J175.9, J176.1, J177.1, J178.1, J180.1, J180.2, LED15.C, R157.2, R162.1, R164.1, R165.1, S30.2, U57.2, U58.2, U59.5, U59.18, U59.35, U59.42, U60.GND@1, U60.GND@2, U60.GND@3
MISO: J11.2, U3.MISO, U4.21
MISO1: J22.2, U7.21, U8.MISO
MISO2: J34.2, U11.21, U12.MISO
MISO3: J46.2, U15.21, U16.MISO
MISO4: J58.2, U19.21, U20.MISO
MISO5: J70.2, U23.21, U24.MISO
MISO6: J82.2, U27.21, U28.MISO
MISO7: J94.2, U31.21, U32.MISO
MISO8: J106.2, U35.21, U36.MISO
MISO9: J118.2, U39.21, U40.MISO
MISO10: J130.2, U43.21, U44.MISO
MISO11: J142.2, U47.21, U48.MISO
MISO12: J154.2, U51.21, U52.MISO
MISO13: J166.2, U55.21, U56.MISO
MISO14: J178.2, U59.21, U60.MISO
MOSI: J11.3, U3.MOSI, U4.19
MOSI1: J22.3, U7.19, U8.MOSI
MOSI2: J34.3, U11.19, U12.MOSI
MOSI3: J46.3, U15.19, U16.MOSI
MOSI4: J58.3, U19.19, U20.MOSI
MOSI5: J70.3, U23.19, U24.MOSI
MOSI6: J82.3, U27.19, U28.MOSI
MOSI7: J94.3, U31.19, U32.MOSI
MOSI8: J106.3, U35.19, U36.MOSI
MOSI9: J118.3, U39.19, U40.MOSI
MOSI10: J130.3, U43.19, U44.MOSI
MOSI11: J142.3, U47.19, U48.MOSI
MOSI12: J154.3, U51.19, U52.MOSI
MOSI13: J166.3, U55.19, U56.MOSI
MOSI14: J178.3, U59.19, U60.MOSI
unnamed: D6.C, R10.2
unnamed: D1.C, R7.2
unnamed: D2.C, R3.2
unnamed: F2.2, J16.2, S2.1
unnamed: R14.1, U2.5
unnamed: C2.2, U4.1, Y1.P$2
unnamed: C3.2, U4.2, Y1.P$1
unnamed: D4.C, R9.2
unnamed: F1.2, J9.2, S1.1
unnamed: D7.C, R17.2
unnamed: R5.1, U1.5
unnamed: LED2.A, R12.1
unnamed: D8.C, R11.2
unnamed: D5.C, R16.2
unnamed: C20.2, U7.1, Y2.P$2
unnamed: C21.2, U7.2, Y2.P$1
unnamed: JP3.1, U3.DIO1
unnamed: JP4.1, U3.DIO2
unnamed: D9.C, R21.2
unnamed: JP1.1, U8.DIO1
unnamed: JP2.1, U8.DIO2
unnamed: F3.2, J28.2, S5.1
unnamed: R25.1, U9.5
unnamed: D12.C, R28.2
unnamed: LED3.A, R24.1
unnamed: D13.C, R23.2
unnamed: D11.C, R27.2
unnamed: C33.2, U11.1, Y3.P$2
unnamed: C34.2, U11.2, Y3.P$1
unnamed: D14.C, R32.2
unnamed: JP5.1, U12.DIO1
unnamed: JP6.1, U12.DIO2
unnamed: F4.2, J40.2, S7.1
unnamed: R36.1, U13.5
unnamed: D17.C, R39.2
unnamed: LED4.A, R35.1
unnamed: D18.C, R34.2
unnamed: LED1.A, R13.1
unnamed: D16.C, R38.2
unnamed: C46.2, U15.1, Y4.P$2
unnamed: C47.2, U15.2, Y4.P$1
unnamed: D19.C, R43.2
unnamed: JP7.1, U16.DIO1
unnamed: JP8.1, U16.DIO2
unnamed: F5.2, J52.2, S9.1
unnamed: R47.1, U17.5
unnamed: D22.C, R50.2
unnamed: LED5.A, R46.1
unnamed: D23.C, R45.2
unnamed: D21.C, R49.2
unnamed: C59.2, U19.1, Y5.P$2
unnamed: C60.2, U19.2, Y5.P$1
unnamed: D24.C, R54.2
unnamed: JP9.1, U20.DIO1
unnamed: JP10.1, U20.DIO2
unnamed: F6.2, J64.2, S11.1
unnamed: R58.1, U21.5
unnamed: D27.C, R61.2
unnamed: LED6.A, R57.1
unnamed: D28.C, R56.2
unnamed: D26.C, R60.2
unnamed: C72.2, U23.1, Y6.P$2
unnamed: C73.2, U23.2, Y6.P$1
unnamed: D29.C, R65.2
unnamed: JP11.1, U24.DIO1
unnamed: JP12.1, U24.DIO2
unnamed: F7.2, J76.2, S13.1
unnamed: R69.1, U25.5
unnamed: D32.C, R72.2
unnamed: LED7.A, R68.1
unnamed: D33.C, R67.2
unnamed: D31.C, R71.2
unnamed: C85.2, U27.1, Y7.P$2
unnamed: C86.2, U27.2, Y7.P$1
unnamed: D34.C, R76.2
unnamed: JP13.1, U28.DIO1
unnamed: JP14.1, U28.DIO2
unnamed: F8.2, J88.2, S15.1
unnamed: R80.1, U29.5
unnamed: D37.C, R83.2
unnamed: LED8.A, R79.1
unnamed: D38.C, R78.2
unnamed: D36.C, R82.2
unnamed: C98.2, U31.1, Y8.P$2
unnamed: C99.2, U31.2, Y8.P$1
unnamed: D39.C, R87.2
unnamed: JP15.1, U32.DIO1
unnamed: JP16.1, U32.DIO2
unnamed: F9.2, J100.2, S17.1
unnamed: R91.1, U33.5
unnamed: D42.C, R94.2
unnamed: LED9.A, R90.1
unnamed: D43.C, R89.2
unnamed: D41.C, R93.2
unnamed: C111.2, U35.1, Y9.P$2
unnamed: C112.2, U35.2, Y9.P$1
unnamed: D44.C, R98.2
unnamed: JP17.1, U36.DIO1
unnamed: JP18.1, U36.DIO2
unnamed: F10.2, J112.2, S19.1
unnamed: R102.1, U37.5
unnamed: D47.C, R105.2
unnamed: LED10.A, R101.1
unnamed: D48.C, R100.2
unnamed: D46.C, R104.2
unnamed: C124.2, U39.1, Y10.P$2
unnamed: C125.2, U39.2, Y10.P$1
unnamed: D49.C, R109.2
unnamed: JP19.1, U40.DIO1
unnamed: JP20.1, U40.DIO2
unnamed: F11.2, J124.2, S21.1
unnamed: R113.1, U41.5
unnamed: D52.C, R116.2
unnamed: LED11.A, R112.1
unnamed: D53.C, R111.2
unnamed: D51.C, R115.2
unnamed: C137.2, U43.1, Y11.P$2
unnamed: C138.2, U43.2, Y11.P$1
unnamed: D54.C, R120.2
unnamed: JP21.1, U44.DIO1
unnamed: JP22.1, U44.DIO2
unnamed: F12.2, J136.2, S23.1
unnamed: R124.1, U45.5
unnamed: D57.C, R127.2
unnamed: LED12.A, R123.1
unnamed: D58.C, R122.2
unnamed: D56.C, R126.2
unnamed: C150.2, U47.1, Y12.P$2
unnamed: C151.2, U47.2, Y12.P$1
unnamed: D59.C, R131.2
unnamed: JP23.1, U48.DIO1
unnamed: JP24.1, U48.DIO2
unnamed: F13.2, J148.2, S25.1
unnamed: R135.1, U49.5
unnamed: D62.C, R138.2
unnamed: LED13.A, R134.1
unnamed: D63.C, R133.2
unnamed: D61.C, R137.2
unnamed: C163.2, U51.1, Y13.P$2
unnamed: C164.2, U51.2, Y13.P$1
unnamed: D64.C, R142.2
unnamed: JP25.1, U52.DIO1
unnamed: JP26.1, U52.DIO2
unnamed: F14.2, J160.2, S27.1
unnamed: R146.1, U53.5
unnamed: D67.C, R149.2
unnamed: LED14.A, R145.1
unnamed: D68.C, R144.2
unnamed: D66.C, R148.2
unnamed: C176.2, U55.1, Y14.P$2
unnamed: C177.2, U55.2, Y14.P$1
unnamed: D69.C, R153.2
unnamed: JP27.1, U56.DIO1
unnamed: JP28.1, U56.DIO2
unnamed: F15.2, J172.2, S29.1
unnamed: R157.1, U57.5
unnamed: D72.C, R160.2
unnamed: LED15.A, R156.1
unnamed: D73.C, R155.2
unnamed: D71.C, R159.2
unnamed: C189.2, U59.1, Y15.P$2
unnamed: C190.2, U59.2, Y15.P$1
unnamed: D74.C, R164.2
unnamed: JP29.1, U60.DIO1
unnamed: JP30.1, U60.DIO2
RAW: D3.C, F1.1, J3.1, Q1.2
RAW1: D10.C, F2.1, J17.1, Q2.2
RAW2: D15.C, F3.1, J29.1, Q3.2
RAW3: D20.C, F4.1, J41.1, Q4.2
RAW4: D25.C, F5.1, J53.1, Q5.2
RAW5: D30.C, F6.1, J65.1, Q6.2
RAW6: D35.C, F7.1, J77.1, Q7.2
RAW7: D40.C, F8.1, J89.1, Q8.2
RAW8: D45.C, F9.1, J101.1, Q9.2
RAW9: D50.C, F10.1, J113.1, Q10.2
RAW10: D55.C, F11.1, J125.1, Q11.2
RAW11: D60.C, F12.1, J137.1, Q12.2
RAW12: D65.C, F13.1, J149.1, Q13.2
RAW13: D70.C, F14.1, J161.1, Q14.2
RAW14: D75.C, F15.1, J173.1, Q15.2
RFM_INT: U3.DIO0, U4.29
RFM_INT1: U7.29, U8.DIO0
RFM_INT2: U11.29, U12.DIO0
RFM_INT3: U15.29, U16.DIO0
RFM_INT4: U19.29, U20.DIO0
RFM_INT5: U23.29, U24.DIO0
RFM_INT6: U27.29, U28.DIO0
RFM_INT7: U31.29, U32.DIO0
RFM_INT8: U35.29, U36.DIO0
RFM_INT9: U39.29, U40.DIO0
RFM_INT10: U43.29, U44.DIO0
RFM_INT11: U47.29, U48.DIO0
RFM_INT12: U51.29, U52.DIO0
RFM_INT13: U55.29, U56.DIO0
RFM_INT14: U59.29, U60.DIO0
RXI: J3.10, U4.16
RXI1: J17.10, U7.16
RXI2: J29.10, U11.16
RXI3: J41.10, U15.16
RXI4: J53.10, U19.16
RXI5: J65.10, U23.16
RXI6: J77.10, U27.16
RXI7: J89.10, U31.16
RXI8: J101.10, U35.16
RXI9: J113.10, U39.16
RXI10: J125.10, U43.16
RXI11: J137.10, U47.16
RXI12: J149.10, U51.16
RXI13: J161.10, U55.16
RXI14: J173.10, U59.16
RX_LED: R10.1, U4.48
RX_LED1: R11.1, U7.48
RX_LED2: R23.1, U11.48
RX_LED3: R34.1, U15.48
RX_LED4: R45.1, U19.48
RX_LED5: R56.1, U23.48
RX_LED6: R67.1, U27.48
RX_LED7: R78.1, U31.48
RX_LED8: R89.1, U35.48
RX_LED9: R100.1, U39.48
RX_LED10: R111.1, U43.48
RX_LED11: R122.1, U47.48
RX_LED12: R133.1, U51.48
RX_LED13: R144.1, U55.48
RX_LED14: R155.1, U59.48
SCK: J11.4, U3.SCK, U4.20
SCK1: J22.4, U7.20, U8.SCK
SCK2: J34.4, U11.20, U12.SCK
SCK3: J46.4, U15.20, U16.SCK
SCK4: J58.4, U19.20, U20.SCK
SCK5: J70.4, U23.20, U24.SCK
SCK6: J82.4, U27.20, U28.SCK
SCK7: J94.4, U31.20, U32.SCK
SCK8: J106.4, U35.20, U36.SCK
SCK9: J118.4, U39.20, U40.SCK
SCK10: J130.4, U43.20, U44.SCK
SCK11: J142.4, U47.20, U48.SCK
SCK12: J154.4, U51.20, U52.SCK
SCK13: J166.4, U55.20, U56.SCK
SCK14: J178.4, U59.20, U60.SCK
SCL: J2.4, U4.32
SCL1: J21.4, U7.32
SCL2: J33.4, U11.32
SCL3: J45.4, U15.32
SCL4: J57.4, U19.32
SCL5: J69.4, U23.32
SCL6: J81.4, U27.32
SCL7: J93.4, U31.32
SCL8: J105.4, U35.32
SCL9: J117.4, U39.32
SCL10: J129.4, U43.32
SCL11: J141.4, U47.32
SCL12: J153.4, U51.32
SCL13: J165.4, U55.32
SCL14: J177.4, U59.32
SDA: J2.3, U4.31
SDA1: J21.3, U7.31
SDA2: J33.3, U11.31
SDA3: J45.3, U15.31
SDA4: J57.3, U19.31
SDA5: J69.3, U23.31
SDA6: J81.3, U27.31
SDA7: J93.3, U31.31
SDA8: J105.3, U35.31
SDA9: J117.3, U39.31
SDA10: J129.3, U43.31
SDA11: J141.3, U47.31
SDA12: J153.3, U51.31
SDA13: J165.3, U55.31
SDA14: J177.3, U59.31
SHLD: J1.SHIELD, J1.SHIELD2, J1.SHIELD3, J1.SHIELD4, J1.SHIELD5, J1.SHIELD6, J1.SHIELD7, J1.SHIELD8, J1.SHIELD9, J1.SHIELD10
SHLD1: J10.SHIELD, J10.SHIELD2, J10.SHIELD3, J10.SHIELD4, J10.SHIELD5, J10.SHIELD6, J10.SHIELD7, J10.SHIELD8, J10.SHIELD9, J10.SHIELD10
SHLD2: J25.SHIELD, J25.SHIELD2, J25.SHIELD3, J25.SHIELD4, J25.SHIELD5, J25.SHIELD6, J25.SHIELD7, J25.SHIELD8, J25.SHIELD9, J25.SHIELD10
SHLD3: J37.SHIELD, J37.SHIELD2, J37.SHIELD3, J37.SHIELD4, J37.SHIELD5, J37.SHIELD6, J37.SHIELD7, J37.SHIELD8, J37.SHIELD9, J37.SHIELD10
SHLD4: J49.SHIELD, J49.SHIELD2, J49.SHIELD3, J49.SHIELD4, J49.SHIELD5, J49.SHIELD6, J49.SHIELD7, J49.SHIELD8, J49.SHIELD9, J49.SHIELD10
SHLD5: J61.SHIELD, J61.SHIELD2, J61.SHIELD3, J61.SHIELD4, J61.SHIELD5, J61.SHIELD6, J61.SHIELD7, J61.SHIELD8, J61.SHIELD9, J61.SHIELD10
SHLD6: J73.SHIELD, J73.SHIELD2, J73.SHIELD3, J73.SHIELD4, J73.SHIELD5, J73.SHIELD6, J73.SHIELD7, J73.SHIELD8, J73.SHIELD9, J73.SHIELD10
SHLD7: J85.SHIELD, J85.SHIELD2, J85.SHIELD3, J85.SHIELD4, J85.SHIELD5, J85.SHIELD6, J85.SHIELD7, J85.SHIELD8, J85.SHIELD9, J85.SHIELD10
SHLD8: J97.SHIELD, J97.SHIELD2, J97.SHIELD3, J97.SHIELD4, J97.SHIELD5, J97.SHIELD6, J97.SHIELD7, J97.SHIELD8, J97.SHIELD9, J97.SHIELD10
SHLD9: J109.SHIELD, J109.SHIELD2, J109.SHIELD3, J109.SHIELD4, J109.SHIELD5, J109.SHIELD6, J109.SHIELD7, J109.SHIELD8, J109.SHIELD9, J109.SHIELD10
SHLD10: J121.SHIELD, J121.SHIELD2, J121.SHIELD3, J121.SHIELD4, J121.SHIELD5, J121.SHIELD6, J121.SHIELD7, J121.SHIELD8, J121.SHIELD9, J121.SHIELD10
SHLD11: J133.SHIELD, J133.SHIELD2, J133.SHIELD3, J133.SHIELD4, J133.SHIELD5, J133.SHIELD6, J133.SHIELD7, J133.SHIELD8, J133.SHIELD9, J133.SHIELD10
SHLD12: J145.SHIELD, J145.SHIELD2, J145.SHIELD3, J145.SHIELD4, J145.SHIELD5, J145.SHIELD6, J145.SHIELD7, J145.SHIELD8, J145.SHIELD9, J145.SHIELD10
SHLD13: J157.SHIELD, J157.SHIELD2, J157.SHIELD3, J157.SHIELD4, J157.SHIELD5, J157.SHIELD6, J157.SHIELD7, J157.SHIELD8, J157.SHIELD9, J157.SHIELD10
SHLD14: J169.SHIELD, J169.SHIELD2, J169.SHIELD3, J169.SHIELD4, J169.SHIELD5, J169.SHIELD6, J169.SHIELD7, J169.SHIELD8, J169.SHIELD9, J169.SHIELD10
STAT_LED: D2.A, U4.26
STAT_LED1: D9.A, U7.26
STAT_LED2: D14.A, U11.26
STAT_LED3: D19.A, U15.26
STAT_LED4: D24.A, U19.26
STAT_LED5: D29.A, U23.26
STAT_LED6: D34.A, U27.26
STAT_LED7: D39.A, U31.26
STAT_LED8: D44.A, U35.26
STAT_LED9: D49.A, U39.26
STAT_LED10: D54.A, U43.26
STAT_LED11: D59.A, U47.26
STAT_LED12: D64.A, U51.26
STAT_LED13: D69.A, U55.26
STAT_LED14: D74.A, U59.26
SWDCLK: TP2.P$1, U4.45
SWDCLK1: TP4.P$1, U7.45
SWDCLK2: TP6.P$1, U11.45
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
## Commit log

2018-08-16 Added Sparkfun labels, correct RFM module (same pinout), fixed silk
2018-08-16 More silk fixes
2018-08-17 RX/TX LED Spacing
2018-08-17 Removed Flash, added standoffs
2018-08-20 Post-checklist
2018-08-22 Post Review fixes
2018-08-23 Issues caught
    Replaced 10k resistors with 1M Ohm resistors, added Mosfet circuit, moved decoupling capacitors in schematic to more clearly reflect their placement on the board, and removed jumper from RAW line. Al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
2018-08-28 Gerbers
2018-09-26 Production Files were inconsitent
2018-10-01 v10
    Cleanup of repo, updated readme.
2018-10-01 License File
2018-10-01 Remove uneccesary files
2018-10-02 These production files doubled up and the incorrect ones.
2019-06-09 Added UF2 Bootloader
2019-10-29 VDDCORE now has 01uF cap to GND
    Previously, it was incorrectly connected to VDDIN (3.3V)
    -bumped version to v11
    -updated gitignore
    -added quiic logo
2019-10-29 included PTH headers for SWD lines
    note, I did not move test points.
2019-10-29 Added LED disable Jumper NC trace
    for easier access to disable Power LED in low power applications
2019-10-30 Changed C7 to 1.0uF as recommended in DS
    This is the VDDCORE cap to GND.
2019-10-30 One GND symbol in old library
2019-10-30 fixing product links in readme
    didn't have the "https://"
2019-10-31 sch stuff
    - removed one extra 3.3V symbol near IC
    - added vcc range to sch near IC
2021-12-30 Fix broken links to datasheet
2023-12-18 Adds correct panel
2024-01-16 Adds new panel
2024-01-16 Renames production zip file with version number
2024-01-16 Updated panel fiducials
2024-01-16 Updated panel zip
2024-01-16 Adds more details to ordering instructions
